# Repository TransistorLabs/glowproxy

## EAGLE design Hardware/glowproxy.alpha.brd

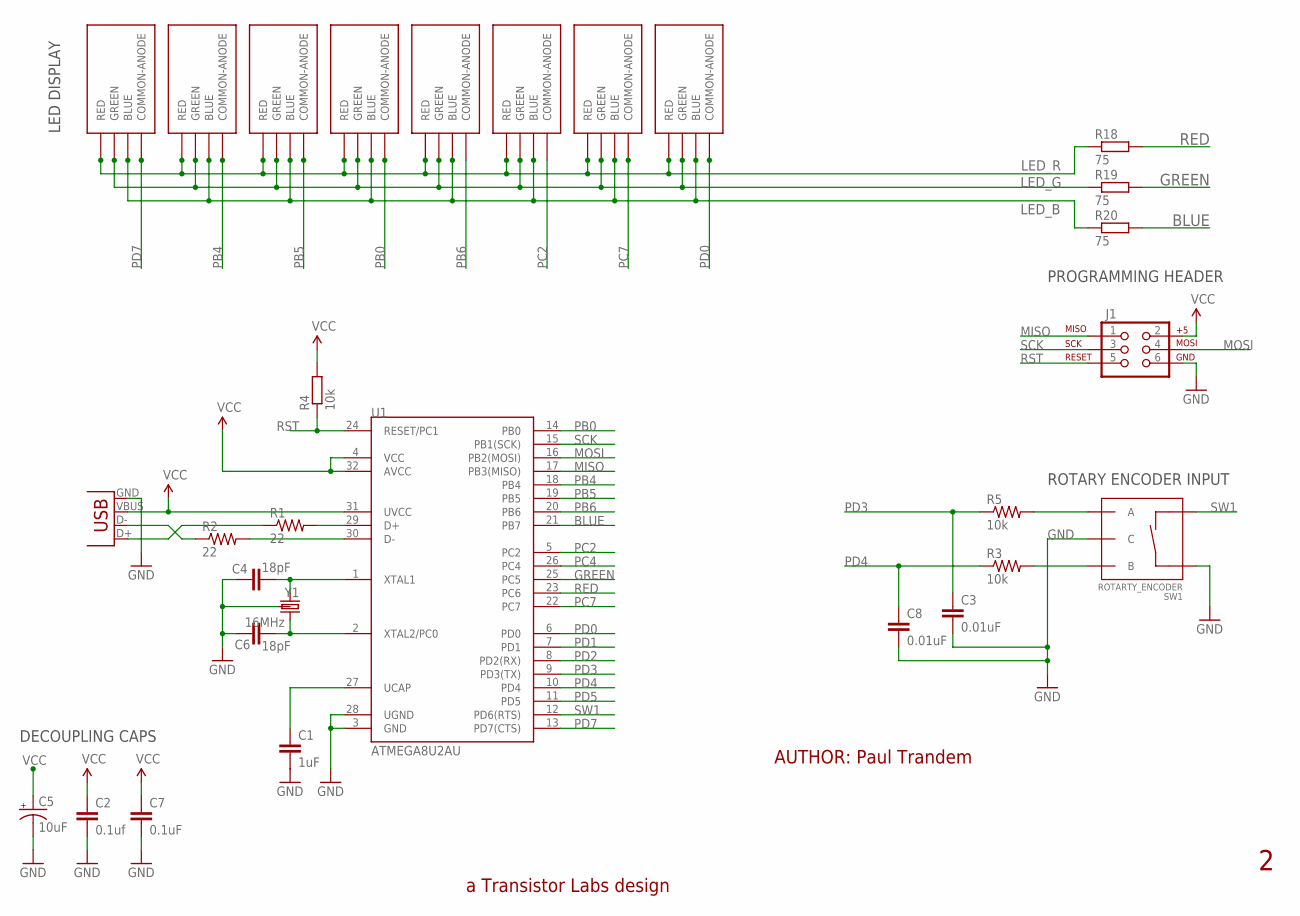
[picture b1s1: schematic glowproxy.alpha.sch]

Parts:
C1: 1uF; C0603
C2: 0.1uf; C0603
C3, C8: 0.01uF; C0603
C4, C6: 18pF; 0603-CAP
C5: 10uF; EIA3216
C7: 0.1uF; C0603
J1: AVR_SPI_PRG_6PTH; 2X3
LED0, LED1, LED2, LED3, LED4, LED5, LED6, LED7: RGB-LED-SMD-CLV1A-FKB
R1, R2: 22; 0603-RES
R3, R5: 10k; 0603-RES
R4: 10k; R0603
R18, R19, R20: 75; R0603
SW1: ROTARTY_ENCODER; ROTARY_ENC_PLAIN
U1: ATMEGA8U2AU; TQFP32-08
X1: USBSMD; USB-MINIB
Y1: 16MHz; CRYSTAL-SMD-5X3

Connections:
BLUE: R20.2, U1.21 (PB7)
DP_N: R2.2, U1.30 (D-)
DP_P: R1.2, U1.29 (D+)
GND: C1.2, C2.2, C3.2, C4.2, C5.C (-), C6.2, C7.2, C8.2, J1.6, SW1.C, SW1.SW+, U1.3 (GND), U1.28 (UGND), X1.GND, Y1.2 (GND), Y1.4 (GND)
GREEN: R19.2, U1.25 (PC5)
LED_B: LED0.BLUE, LED1.BLUE, LED2.BLUE, LED3.BLUE, LED4.BLUE, LED5.BLUE, LED6.BLUE, LED7.BLUE, R20.1
LED_G: LED0.GREEN, LED1.GREEN, LED2.GREEN, LED3.GREEN, LED4.GREEN, LED5.GREEN, LED6.GREEN, LED7.GREEN, R19.1
LED_R: LED0.RED, LED1.RED, LED2.RED, LED3.RED, LED4.RED, LED5.RED, LED6.RED, LED7.RED, R18.1
MISO: J1.1, U1.17 (PB3(MISO))
MOSI: J1.4, U1.16 (PB2(MOSI))
unnamed: R5.2, SW1.A
unnamed: R3.2, SW1.B
unnamed: C4.1, U1.1 (XTAL1), Y1.3 (2)
unnamed: C6.1, U1.2 (XTAL2/PC0), Y1.1
unnamed: C1.1, U1.27 (UCAP)
PB0: LED4.COMMON-ANODE, U1.14 (PB0)
PB4: LED0.COMMON-ANODE, U1.18 (PB4)
PB5: LED7.COMMON-ANODE, U1.19 (PB5)
PB6: LED5.COMMON-ANODE, U1.20 (PB6)
PC2: LED1.COMMON-ANODE, U1.5 (PC2)
PC4: U1.26 (PC4)
PC7: LED6.COMMON-ANODE, U1.22 (PC7)
PD0: LED2.COMMON-ANODE, U1.6 (PD0)
PD1: U1.7 (PD1)
PD2: U1.8 (PD2(RX))
PD3: C3.1, R5.1, U1.9 (PD3(TX))
PD4: C8.1, R3.1, U1.10 (PD4)
PD5: U1.11 (PD5)
PD7: LED3.COMMON-ANODE, U1.13 (PD7(CTS))
RED: R18.2, U1.23 (PC6)
RST: J1.5, R4.1, U1.24 (RESET/PC1)
SCK: J1.3, U1.15 (PB1(SCK))
SW1: SW1.SW-, U1.12 (PD6(RTS))
USBD_N: R2.1, X1.D-
USBD_P: R1.1, X1.D+
VCC: C2.1, C5.A (+), C7.1, J1.2, R4.2, U1.4 (VCC), U1.31 (UVCC), U1.32 (AVCC), X1.VBUS

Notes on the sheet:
a Transistor Labs design
AUTHOR: Paul Trandem
PROGRAMMING HEADER
LED DISPLAY
DECOUPLING CAPS
ROTARY ENCODER INPUT

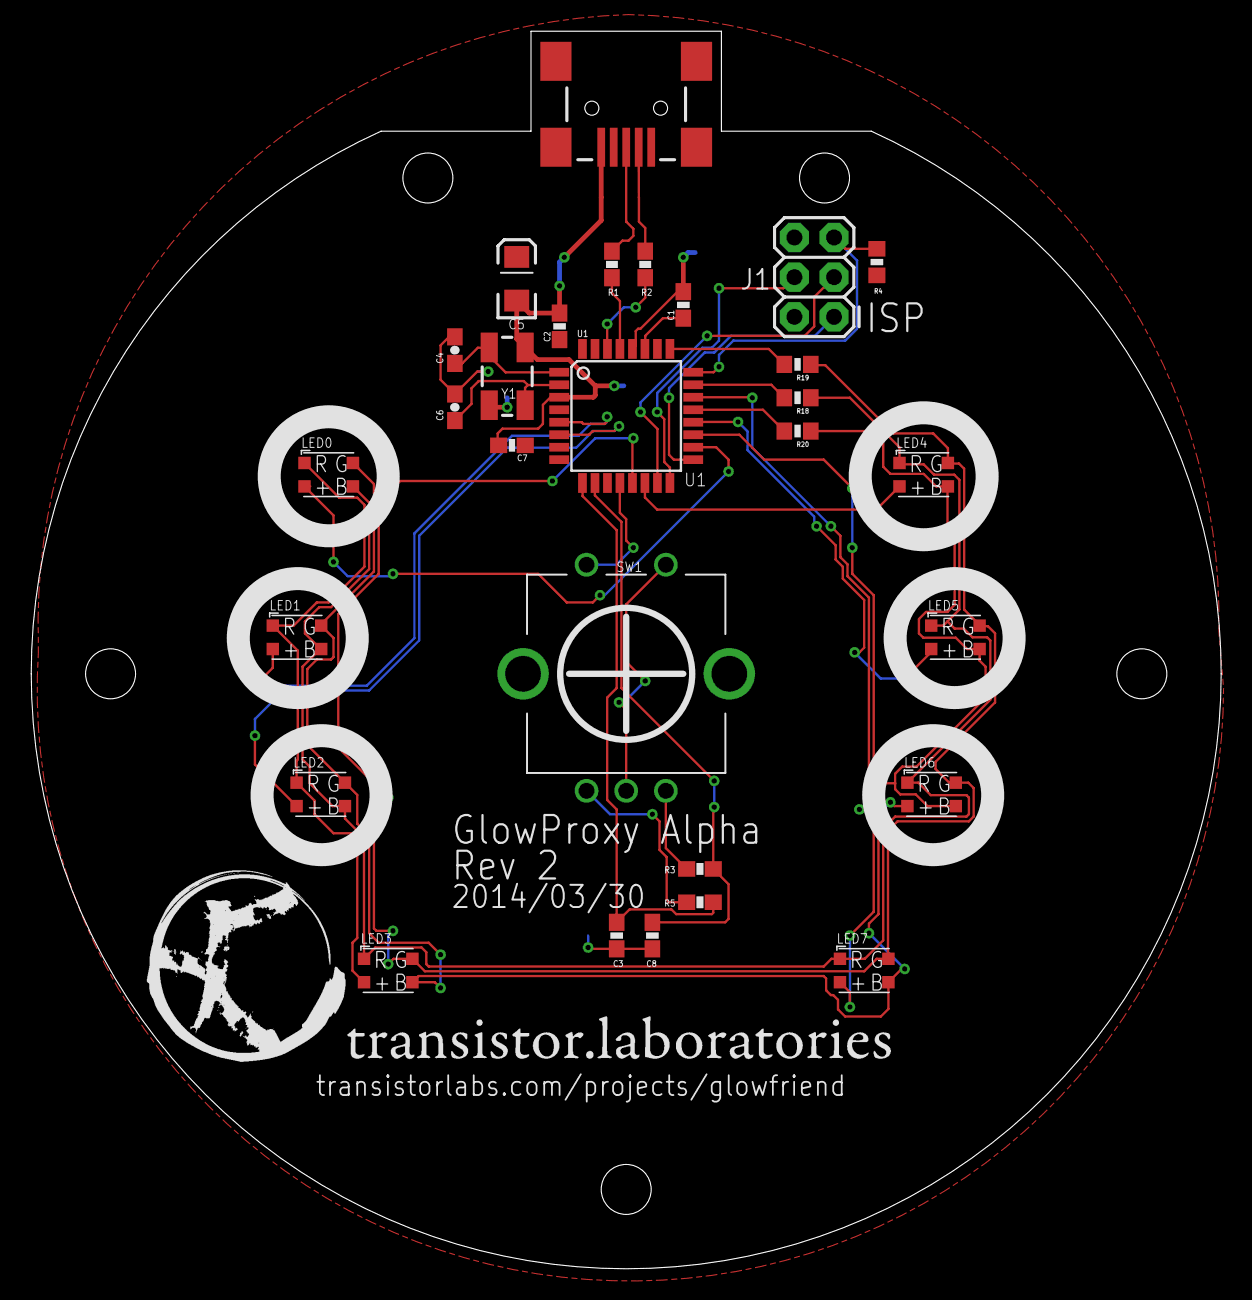
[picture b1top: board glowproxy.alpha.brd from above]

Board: 2 copper layers, 76.2 x 79.2 mm, 31 parts (1 on the bottom side), 32 nets.

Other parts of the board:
U$1, U$2: TL-LOGO

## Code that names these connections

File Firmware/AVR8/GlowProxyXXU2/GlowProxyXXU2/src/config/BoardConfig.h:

/*
 * BoardConfig.h
 * Configuration Settings for the target board of GlowProxy Alpha
 * Includes port settings, etc
 *  Author: paul
 */ 

#include <avr/io.h>

#ifndef BOARDCONFIG_H_
#define BOARDCONFIG_H_

#define BOARDCONFIG_LEDCOUNT	8

#define LED0PIN		PB4
#define LED1PIN		PC2
#define LED2PIN		PD0
#define LED3PIN		PD7
#define LED4PIN		PB0
#define LED5PIN		PB6
#define LED6PIN		PC7
#define LED7PIN		PB5

#define LED0PORT	&PORTB
#define LED1PORT	&PORTC
#define LED2PORT	&PORTD
#define LED3PORT	&PORTD
#define LED4PORT	&PORTB
#define LED5PORT	&PORTB
#define LED6PORT	&PORTC
#define LED7PORT	&PORTB

#define ENCODER_PINS			PIND
#define ENCODER_PORT			PORTD
#define ENCODER_PORTDIRECTION	DDRD

#define	ENCODER_PIN_A			PD3
#define	ENCODER_PIN_B			PD4
#define	ENCODER_SW				PD6

// Used for masking the debouncer output
static const uint8_t ENCODER_PORTMASK = (1<<ENCODER_PIN_A) | (1<<ENCODER_PIN_B) | (1 << ENCODER_SW);
static const uint8_t ENCODER_ROTATIONPINS_BITMASK = (1<<ENCODER_PIN_A) | (1<<ENCODER_PIN_B);
static const uint8_t ENCODER_BUTTON_BITMASK = (1<<ENCODER_SW);

#define RED	OCR1A // PC6
#define GRN	OCR1B // PC5
#define BLU	OCR1C // PB7


void BoardConfig_Init(void);


#endif /* BOARDCONFIG_H_ */

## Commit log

2014-03-18 initial commit of firmware with somewhat-working encoder logic
2014-04-18 migrating from 8u2 to 32u2; adding basic led drivers
2014-04-18 adding hardware files
2014-04-18 adding windows desktop shell - TODO: clean up gitignore and remove bins, etc
2014-04-18 adding design/drawing files
2014-04-22 more stuff. wow, i really need to clean up this repo
2014-04-28 iteration and stuff.
2014-05-04 Adding base network infrastructure
2014-05-04 Hooking up the USB events to the network events
2014-05-04 cambam files
2014-05-04 adding dependencies
2014-06-06 rebuilding release libs and other stuff I don't remember... day-job-quality checkin this is not.
2014-06-06 adding an SUO file i should really be ignoring; adding some nuget configs; adding a CamBam file
2014-06-06 adding... some logic, presumably.
2014-06-06 adding a timer to throttling service inputs... so much badness

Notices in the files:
parts and their libraries:
SparkFun-Electromechanical: Licensing: CC v3.0 Share-Alike You are welcome to use this library for commercial purposes.
